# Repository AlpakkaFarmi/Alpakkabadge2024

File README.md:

# Alpakkabadge2024

Alpakkabadge2024 - Created originally for Disobey 2024

Schematic: https://github.com/AlpakkaFarmi/Alpakkabadge2024/blob/main/hw/alpakkabadge_schematic_v6.pdf

Binary: https://github.com/AlpakkaFarmi/Alpakkabadge2024/releases/download/1.0/alpakkabadge.uf2

# Getting Started

## 1. Remove battery power

CR2032 is not powerful enough to feed the Pico and three RGB-LEDs, so it is wiser to power the badge via USB or the dedicated power input pads.

To ensure that the battery is not charged from the external power supply, it is essential to cut the jumper below the battery holder.

## 2. Remove three resistors

There are three resistors located inside the Pico footprint.
The red LEDs are connected to GND via three resistors. These resistors keep the LEDs on when the battery is inserted.

To allow Pico to control these red LEDs, remove these three resistors.

## 3. Solder Pico

Add solder to one corner of the Pico footprint and align Pico with the pads. This way you can still adjust board position by heating the soldered pad.

When Pico is aligned, solder all other pads.

## 4. Program Pico

Connect Pico to computer while holding the BOOTSEL-button.
You should see new mass memory device appearing.

Copy the latest release from this repo to Pico and the badge should reboot with blinking lights.

# Building Firmware

## Development prerequisites

Install Rust https://www.rust-lang.org/

## Build

Connect pico into computer in bootmode and run `run` to build and deploy of the firmware

    cargo run --release

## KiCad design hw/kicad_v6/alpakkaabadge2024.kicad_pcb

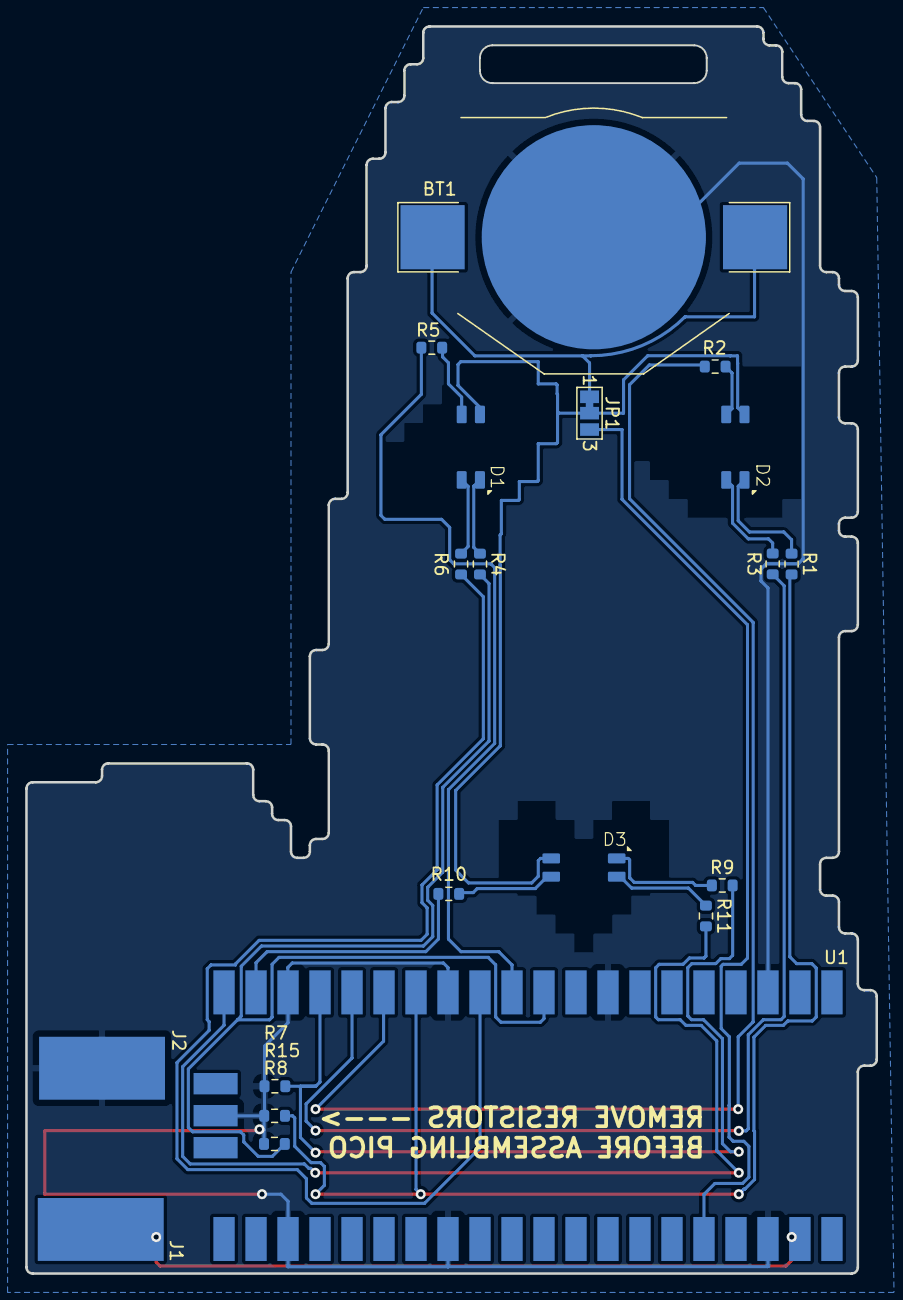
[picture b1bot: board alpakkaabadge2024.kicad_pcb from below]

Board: 2 copper layers, 67.5 x 99.0 mm, 20 parts (20 on the bottom side), 23 nets.

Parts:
BT1: CR2024; BatteryHolder_Keystone_3002_1x2032
D1, D2, D3: XZMDKCBDDG45S-9; RGB LED
J1: PICO POWER INPUT; SolderWirePad_1x01_SMD_5x10mm
J2: (3-5.5V); SolderWirePad_1x01_SMD_5x10mm
JP1: POWER INPUT SELECT; SolderJumper-3_P1.3mm_Bridged12_Pad1.0x1.5mm_NumberLabels
R1, R4, R9: 140R; R_0603_1608Metric
R2, R3, R5, R6, R10, R11: 30R; R_0603_1608Metric
R7, R8, R15: 60.4; R_0603_1608Metric
U1: Pico; RPi_Pico_SMD_TH

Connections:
+BATT: BT1.1 (+), JP1.1 (A)
GND: BT1.2 (-), J2.1, R7.1, R8.1, R15.1, U1.3 (GND), U1.8 (GND), U1.13 (GND), U1.18 (GND), U1.23 (GND), U1.28 (GND), U1.38 (GND), U1.42 (GND)
HEART_BLUE: R10.2, U1.19 (GPIO14)
HEART_GREEN: R11.2, U1.20 (GPIO15)
HEART_RED: R7.2, R9.2, U1.17 (GPIO13)
LEFT_BLUE: R5.2, U1.11 (GPIO8)
LEFT_GREEN: R6.2, U1.12 (GPIO9)
LEFT_RED: R4.2, R8.2, U1.10 (GPIO7)
unnamed: D1.3 (BLUE), R5.1
unnamed: D1.4 (GREEN), R6.1
unnamed: D1.1 (RED), R4.1
unnamed: D2.3 (BLUE), R2.1
unnamed: D2.4 (GREEN), R3.1
unnamed: D2.1 (RED), R1.1
unnamed: D3.3 (BLUE), R10.1
unnamed: D3.4 (GREEN), R11.1
unnamed: D3.1 (RED), R9.1
PICO_3V3_OUT: JP1.3 (B), U1.36 (3V3)
PICO_PWR_IN: J1.1, U1.39 (VSYS)
PWM5A: R1.2, R15.2, U1.14 (GPIO10)
PWM5B: R2.2, U1.15 (GPIO11)
PWM6A: R3.2, U1.16 (GPIO12)
VDD: D1.2 (A), D2.2 (A), D3.2 (A), JP1.2 (C)

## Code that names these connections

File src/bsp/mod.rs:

pub mod prelude;

pub use rp2040_hal as hal;

#[link_section = ".boot2"]
#[no_mangle]
#[used]
pub static BOOT2_FIRMWARE: [u8; 256] = rp2040_boot2::BOOT_LOADER_W25Q080;

hal::bsp_pins!(Gpio25 {
    name: led,
    aliases: { PushPullOutput: Led }
},Gpio7 {
    name: pwm7,
    aliases: { FunctionPwm: PWM7 }
},Gpio8 {
    name: pwm8,
    aliases: { FunctionPwm: PWM8 }
},Gpio9 {
    name: pwm9,
    aliases: { FunctionPwm: PWM9 }
},Gpio10 {
    name: pwm10,
    aliases: { FunctionPwm: PWM10 }
},Gpio11 {
    name: pwm11,
    aliases: { FunctionPwm: PWM11 }
},Gpio12 {
    name: pwm12,
    aliases: { FunctionPwm: PWM12 }
},Gpio13 {
    name: pwm13,
    aliases: { FunctionPwm: PWM13 }
},Gpio14 {
    name: pwm14,
    aliases: { FunctionPwm: PWM14 }
},Gpio15 {
    name: pwm15,
    aliases: { FunctionPwm: PWM15 }
},);

pub const XOSC_CRYSTAL_FREQ: u32 = 12_000_000;

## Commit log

2024-02-18 adding code
2024-02-18 Added hardware files
